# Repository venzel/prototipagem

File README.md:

### Projeto final da disciplina de Prototipage IFPB

O projeto faz parte da disciplina **Técnicas de Prototipagem**, em **Engenharia de Computação, IFPB**, ministrada pelos Professores **Dr. Moacy Pereira da Silva** e **Dr. Alexandre Sales Vasconcelos**. <br /><br />

### Equipe

-   Diego Alex Maia de Lima
-   Edivam Enéas de Almeida Júnior<br /><br />

# PROJETO DE SISTEMA DE AQUISIÇÃO DE DADOS

### Projeto

O projeto consite no desenvolvimento de um shield para arduíno, com a principal funcionalidade na aquisição de dados mediante temperaturas de aquecimento. <br /><br />

### Sobre o shield

O shield é composto de três funcionalidades, sendo elas, um sistema de aquecimento, um sistema de controle de velocidade de motor com auxílio de transmissores e receptores infravermelhos e um sistema de conversão de um sinal analógico para um PWM que alimenta um led, configurando uma forma iterativa de observar e manipular a duração do pulso em nível lógico alto ou baixo de acordo com o nível de luminosidade do led.<br /><br />

👉 <a href="https://a360.co/3w6mWB6" target="_blank">Link do projeto 3D</a><br /><br />

### Componentes utilizados

-   2 LM35
-   2 TIP31C
-   2 resistores 470hms
-   1 resistor 330hms
-   1 resistor 10khms
-   2 resistores 220hms
-   2 leds
-   1 Led infravermelho IR - TX/RX
-   1 Potenciômetro
-   1 motor dc (cooler)<br /><br />

### Download dos arquivos

👉 <a href="https://github.com/venzel/shield_dados/raw/master/arquivos/pcb/esquematico.zip" target="_blank">Arquivos do projeto</a><br />

👉 <a href="https://github.com/venzel/shield_dados/blob/master/arquivos/doc/documento.pdf" target="_blank">Documento em PDF do projeto</a><br /><br />

### Esquemático do circuito

<br /><br />

### Trilhas e Layer

<br /><br />

<br /><br />

<br /><br />

### Esquemático 3D

<br /><br />

<br /><br />

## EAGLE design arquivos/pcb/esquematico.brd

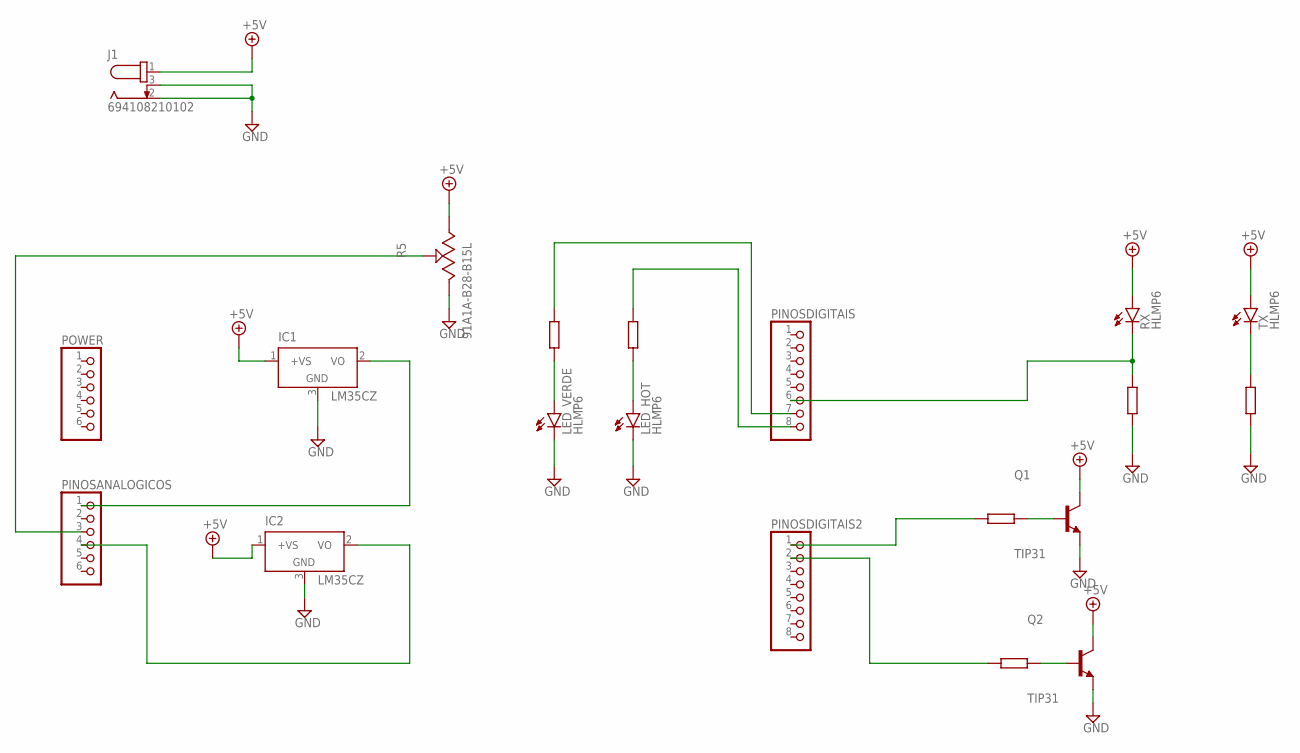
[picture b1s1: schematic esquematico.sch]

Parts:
IC1, IC2: LM35CZ; TO92
J1: 694108210102
LED_HOT: HLMP6
LED_VERDE: HLMP6
PINOSANALOGICOS: PINHD-1X6; 1X06
PINOSDIGITAIS, PINOSDIGITAIS2: PINHD-1X8; 1X08
POWER: PINHD-1X6; 1X06
Q1, Q2: TIP31; TO254P1060X482X2222-3
R5: 91A1A-B28-B15L; 91A1A-B28-B15L-ND
RX: HLMP6
TX: HLMP6

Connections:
+5V: IC1.1 (+VS), IC2.1 (+VS), J1.1, Q1.2 (C), Q2.2 (C), R5.3, RX.A, TX.A
GND: IC1.3 (GND), IC2.3 (GND), J1.2, J1.3, LED_HOT.K, LED_VERDE.K, Q1.3 (E), Q2.3 (E), R5.1
unnamed: IC2.2 (VO), PINOSANALOGICOS.4
unnamed: PINOSDIGITAIS.6, RX.K
unnamed: PINOSANALOGICOS.3, R5.2
unnamed: IC1.2 (VO), PINOSANALOGICOS.1

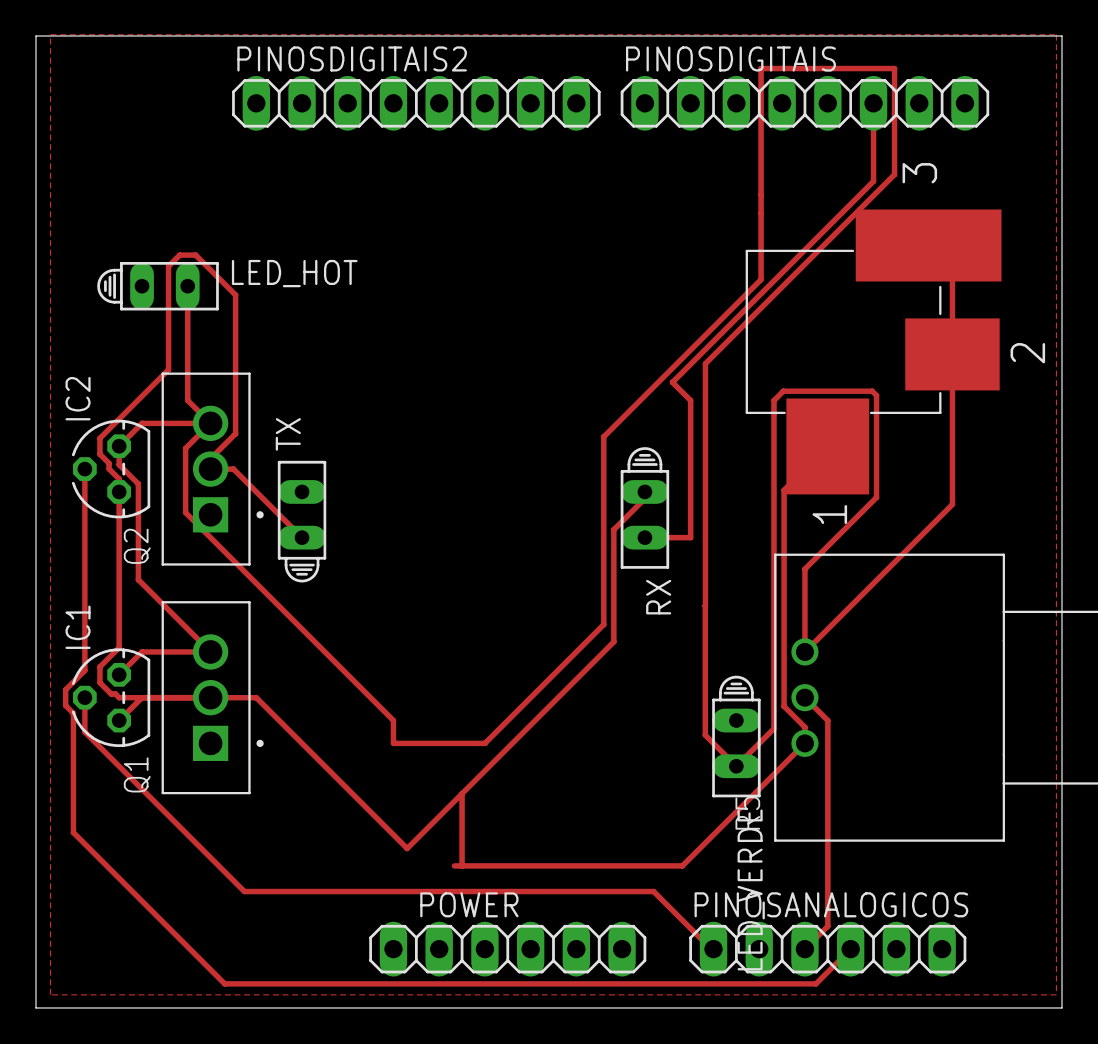
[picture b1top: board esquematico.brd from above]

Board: 2 copper layers, 57.0 x 54.0 mm, 14 parts (0 on the bottom side), 6 nets.

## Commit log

2021-05-16 inicio do commit...
2021-05-16 projeto v1
2021-05-16 projeto v2
2021-05-16 projeto v3
2021-05-16 projeto v4
2021-05-16 projeto v5
2021-05-16 projeto v6
2021-05-16 projeto v7
2021-05-16 projeto v8
2021-05-16 projeto v9
2021-05-16 projeto v10
2021-05-16 projeto v11
2021-05-16 projeto v12
2021-05-16 projeto v13
2021-05-16 projeto v14
2021-05-17 Documento...
2021-05-21 Esquematico atualizado
2022-03-19 Create LICENSE
2022-03-19 docs: altera a readme v1
